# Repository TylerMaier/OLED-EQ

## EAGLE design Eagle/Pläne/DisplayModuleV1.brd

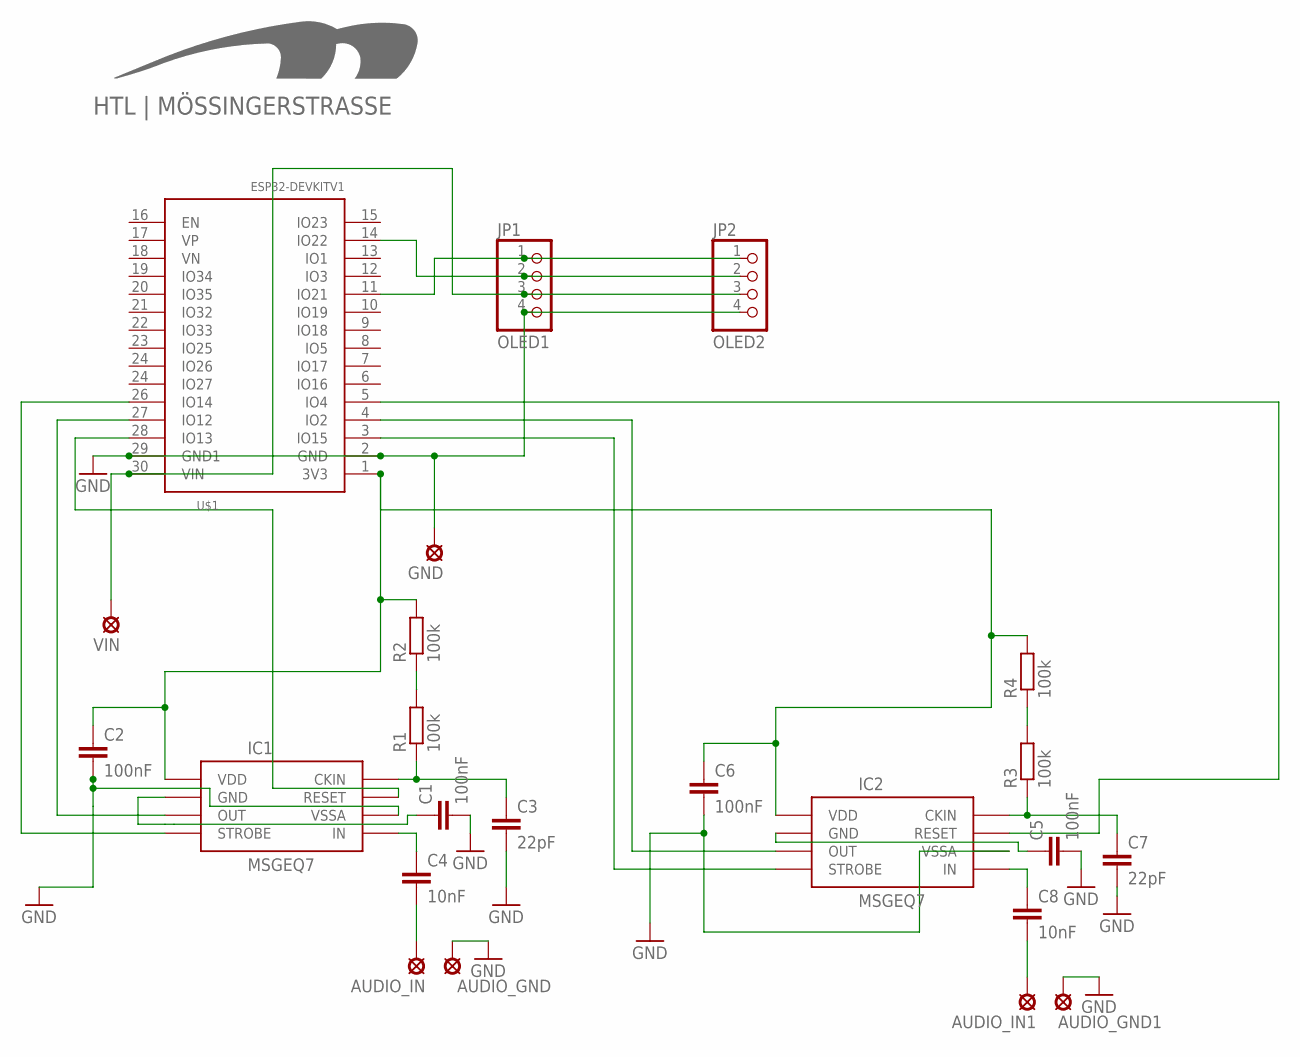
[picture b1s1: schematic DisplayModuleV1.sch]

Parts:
AUDIO_GND, AUDIO_GND1: LSP10
AUDIO_IN, AUDIO_IN1: LSP10
C1, C2, C5, C6: 100nF; C050-030X075
C3, C7: 22pF; C050-030X075
C4, C8: 10nF; C050-030X075
GND: LSP10
IC1, IC2: MSGEQ7DIP; DIL08
JP1: OLED1; 1X04
JP2: OLED2; 1X04
R1, R2, R3, R4: 100k; 0204/7
U$1: ESP32DEVKITV1; ESP32-DEVKITV1
U$2: HTL_LOGOBOTTOP_15MM; LOGO_15
VIN: LSP10

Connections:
GND: AUDIO_GND.MP, AUDIO_GND1.MP, C1.2, C2.2, C3.2, C5.2, C6.2, C7.2, GND.MP, IC1.2 (VSSA), IC2.2 (VSSA), JP1.4, JP2.4, U$1.2 (GND), U$1.29 (GND1)
unnamed: C2.1, C6.1, IC1.1 (VDD), IC2.1 (VDD), R2.2, R4.2, U$1.1 (3V3)
unnamed: R1.2, R2.1
unnamed: C3.1, IC1.8 (CKIN), R1.1
unnamed: IC1.7 (RESET), U$1.28 (IO13)
unnamed: IC1.3 (OUT), U$1.27 (IO12)
unnamed: IC1.4 (STROBE), U$1.26 (IO14)
unnamed: C1.1, IC1.6 (GND)
unnamed: C4.1, IC1.5 (IN)
unnamed: AUDIO_IN.MP, C4.2
unnamed: IC2.7 (RESET), U$1.5 (IO4)
unnamed: R3.2, R4.1
unnamed: C7.1, IC2.8 (CKIN), R3.1
unnamed: IC2.3 (OUT), U$1.4 (IO2)
unnamed: IC2.4 (STROBE), U$1.3 (IO15)
unnamed: C5.1, IC2.6 (GND)
unnamed: C8.1, IC2.5 (IN)
unnamed: AUDIO_IN1.MP, C8.2
unnamed: JP1.1, JP2.1, U$1.11 (IO21)
unnamed: JP1.2, JP2.2, U$1.14 (IO22)
unnamed: JP1.3, JP2.3, U$1.30 (VIN), VIN.MP

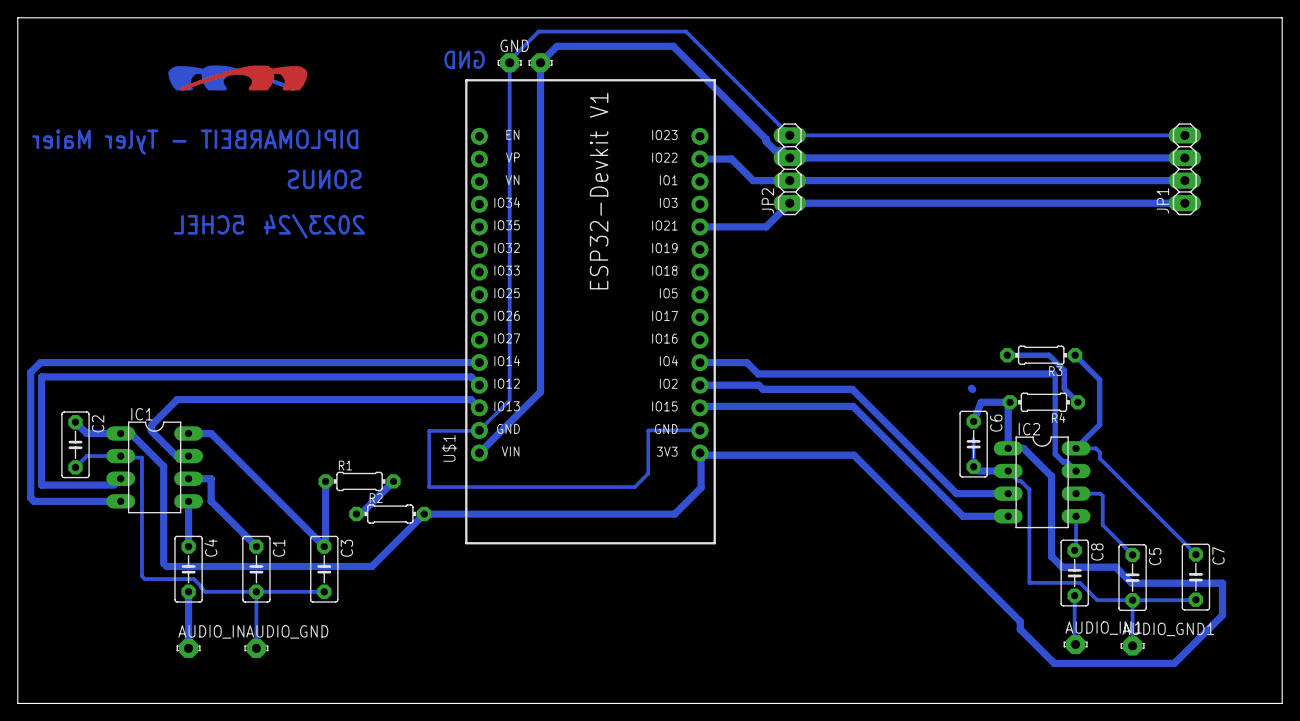
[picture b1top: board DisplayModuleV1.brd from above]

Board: 2 copper layers, 142.0 x 77.0 mm, 24 parts (0 on the bottom side), 21 nets.
